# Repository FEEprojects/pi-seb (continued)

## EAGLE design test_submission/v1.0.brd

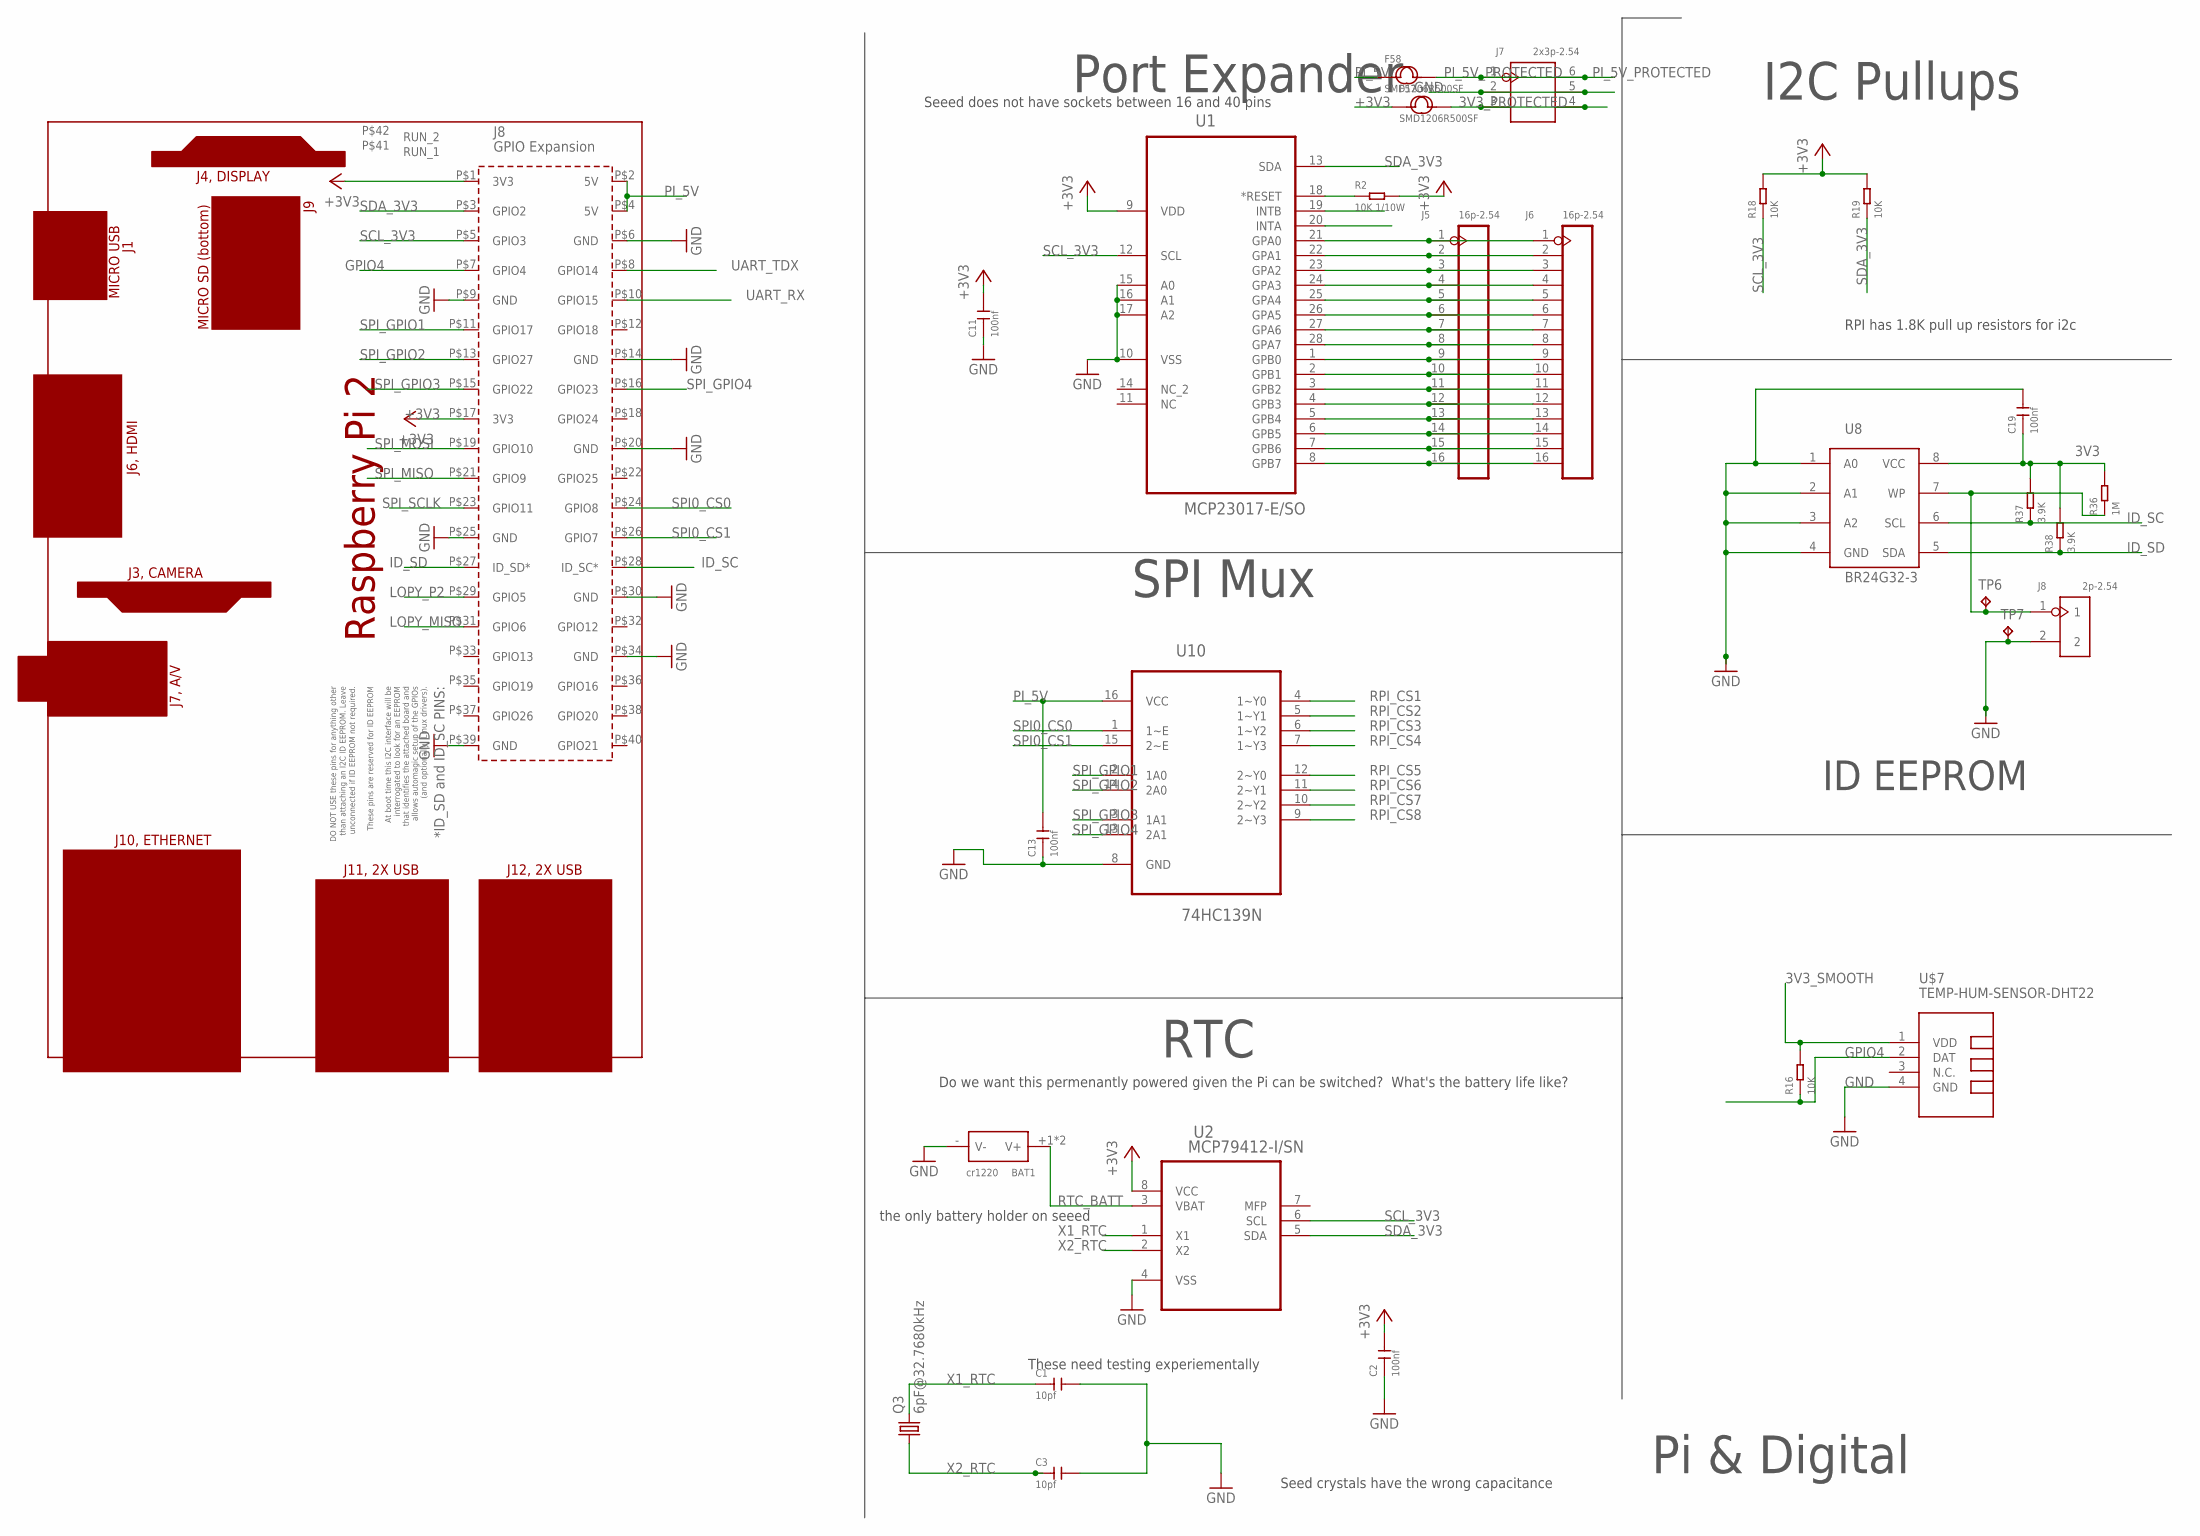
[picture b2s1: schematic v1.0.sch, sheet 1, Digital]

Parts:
BAT1: cr1220; BAT2P-13.5-CR1220
C1, C3: 10pf; C0603
C2, C11, C13, C19: 100nf; C0603
F57, F58: SMD1206R500SF; F1206
J5, J6: 16p-2.54; H16-2.54
J7: 2x3p-2.54; H2X3-2.54
J8: 2p-2.54; H2-2.54
PCB1: RPI2
Q3: 6pF@32.7680kHz; 86SMX
R2: 10K 1/10W; R0603
R16, R18, R19: 10K; R0603
R36: 1M; R0603
R37, R38: 3.9K; R0603
TP6, TP7: TPB2,54; B2,54
U1: MCP23017-E/SO; SOIC127P1032X265-28N
U2: MCP79412-I/SN; SOIC127P600X175-8N
U8: BR24G32-3; SOP8
U10: 74HC139N; DIP254P762X420-16
U$7: TEMP-HUM-SENSOR-DHT22

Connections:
3V3: C19.1, R36.2, R37.2, R38.2, U8.8 (VCC)
3V3_PROTECTED: F57.2, J7.3, J7.4
3V3_SMOOTH: R16.2, U$7.1 (VDD); also elsewhere on the board
+3V3: C2.2, C11.2, F57.1, PCB1.P$1 (3V3), PCB1.P$17 (3V3), R2.2, R18.2, R19.2, U1.9 (VDD), U2.8 (VCC); also elsewhere on the board
GND: BAT1.- (V-), C1.2, C2.1, C3.2, C11.1, C13.1, C19.2, J7.2, J7.5, J8.2, PCB1.P$6 (GND), PCB1.P$9 (GND), PCB1.P$14 (GND), PCB1.P$20 (GND), PCB1.P$25 (GND), PCB1.P$30 (GND), PCB1.P$34 (GND), PCB1.P$39 (GND), TP7.TP, U1.10 (VSS), U1.15 (A0), U1.16 (A1), U1.17 (A2), U2.4 (VSS), U8.1 (A0), U8.2 (A1), U8.3 (A2), U8.4 (GND), U10.8 (GND), U$7.4 (GND); also elsewhere on the board
GPIO4: PCB1.P$7 (GPIO4), R16.1, U$7.2 (DAT)
ID_SC: PCB1.P$28 (ID_SC*), R37.1, U8.6 (SCL)
ID_SD: PCB1.P$27 (ID_SD*), R38.1, U8.5 (SDA)
LOPY_MISO: PCB1.P$31 (GPIO6); also elsewhere on the board
LOPY_P2: PCB1.P$29 (GPIO5); also elsewhere on the board
unnamed: R2.1, U1.18 (*RESET)
unnamed: J5.1, J6.1, U1.21 (GPA0)
unnamed: J5.2, J6.2, U1.22 (GPA1)
unnamed: J5.3, J6.3, U1.23 (GPA2)
unnamed: J5.4, J6.4, U1.24 (GPA3)
unnamed: J5.5, J6.5, U1.25 (GPA4)
unnamed: J5.6, J6.6, U1.26 (GPA5)
unnamed: J5.7, J6.7, U1.27 (GPA6)
unnamed: J5.8, J6.8, U1.28 (GPA7)
unnamed: J5.9, J6.9, U1.1 (GPB0)
unnamed: J5.10, J6.10, U1.2 (GPB1)
unnamed: J5.11, J6.11, U1.3 (GPB2)
unnamed: J5.12, J6.12, U1.4 (GPB3)
unnamed: J5.13, J6.13, U1.5 (GPB4)
unnamed: J5.14, J6.14, U1.6 (GPB5)
unnamed: J5.15, J6.15, U1.7 (GPB6)
unnamed: J5.16, J6.16, U1.8 (GPB7)
unnamed: J8.1, R36.1, TP6.TP, U8.7 (WP)
PI_5V: C13.2, F58.1, PCB1.P$2 (5V), PCB1.P$4 (5V), U10.16 (VCC); also elsewhere on the board
PI_5V_PROTECTED: F58.2, J7.1, J7.6
RPI_CS1: U10.4 (1~Y0); also elsewhere on the board
RPI_CS2: U10.5 (1~Y1); also elsewhere on the board
RPI_CS3: U10.6 (1~Y2); also elsewhere on the board
RPI_CS4: U10.7 (1~Y3); also elsewhere on the board
RPI_CS5: U10.12 (2~Y0); also elsewhere on the board
RPI_CS6: U10.11 (2~Y1); also elsewhere on the board
RPI_CS7: U10.10 (2~Y2); also elsewhere on the board
RPI_CS8: U10.9 (2~Y3); also elsewhere on the board
RTC_BATT: BAT1.+1 (V+), BAT1.+2 (V+), U2.3 (VBAT)
SCL_3V3: PCB1.P$5 (GPIO3), R18.1, U1.12 (SCL), U2.6 (SCL); also elsewhere on the board
SDA_3V3: PCB1.P$3 (GPIO2), R19.1, U1.13 (SDA), U2.5 (SDA); also elsewhere on the board
SPI0_CS0: PCB1.P$24 (GPIO8), U10.1 (1~E)
SPI0_CS1: PCB1.P$26 (GPIO7), U10.15 (2~E)
SPI_GPIO1: PCB1.P$11 (GPIO17), U10.2 (1A0)
SPI_GPIO2: PCB1.P$13 (GPIO27), U10.14 (2A0)
SPI_GPIO3: PCB1.P$15 (GPIO22), U10.3 (1A1)
SPI_GPIO4: PCB1.P$16 (GPIO23), U10.13 (2A1)
SPI_MISO: PCB1.P$21 (GPIO9); also elsewhere on the board
SPI_MOSI: PCB1.P$19 (GPIO10); also elsewhere on the board
SPI_SCLK: PCB1.P$23 (GPIO11); also elsewhere on the board
UART_RX: PCB1.P$10 (GPIO15); also elsewhere on the board
UART_TDX: PCB1.P$8 (GPIO14); also elsewhere on the board
X1_RTC: C1.1, Q3.4 (2), U2.1 (X1)
X2_RTC: C3.1, Q3.1, U2.2 (X2)

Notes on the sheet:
Pi & Digital
Port Expander
SPI Mux
RTC
I2C Pullups
Do we want this permenantly powered given the Pi can be switched? What's the battery life like?
Seed crystals have the wrong capacitance
These need testing experiementally
Seeed does not have sockets between 16 and 40 pins
RPI has 1.8K pull up resistors for i2c
the only battery holder on seeed
ID EEPROM

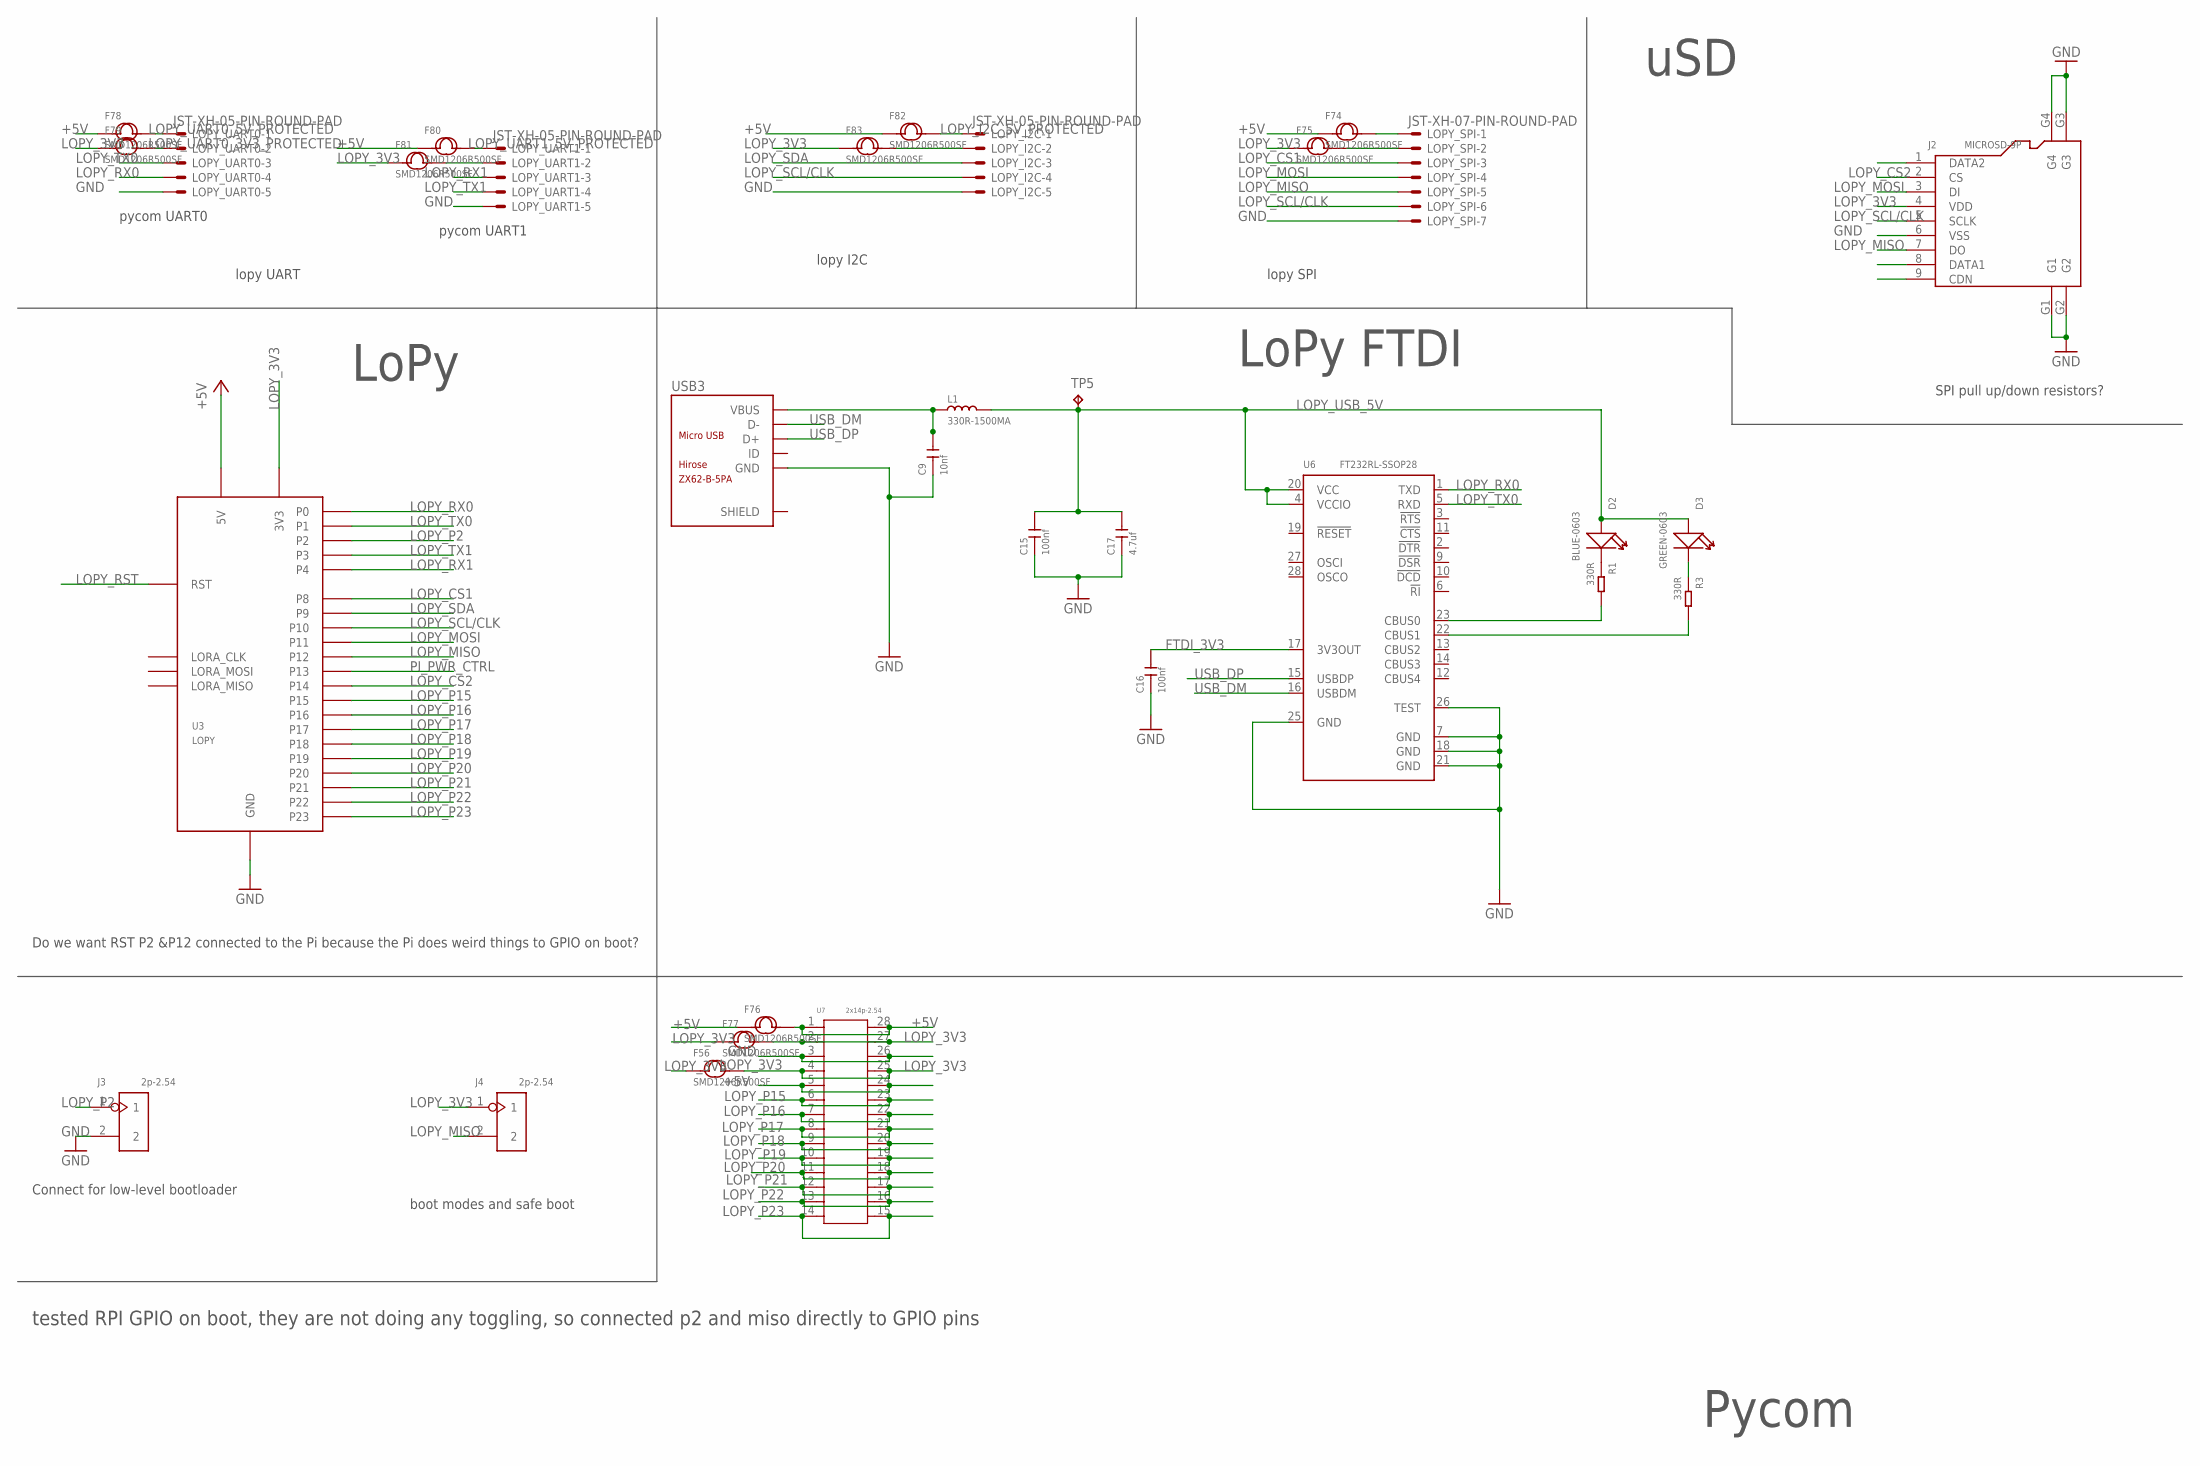
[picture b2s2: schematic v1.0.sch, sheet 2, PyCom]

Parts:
C9: 10nf; C0805
C15, C16: 100nf; C0603
C17: 4.7uf; C0603
D2: BLUE-0603; LED-0603
D3: GREEN-0603; LED-0603
F56, F74, F75, F76, F77, F78, F79, F80, F81, F82, F83: SMD1206R500SF; F1206
J2: MICROSD-9P; MICRO-SD9+4P-SMD-16.1X14.5X1.85MM
J3, J4: 2p-2.54; H2-2.54
L1: 330R-1500MA; L0805
LOPY_I2C: JST-XH-05-PIN-ROUND-PAD; JST-XH-05-PACKAGE-ROUND-PAD
LOPY_SPI: JST-XH-07-PIN-ROUND-PAD; JST-XH-07-PACKAGE-ROUND-PAD
LOPY_UART0, LOPY_UART1: JST-XH-05-PIN-ROUND-PAD; JST-XH-05-PACKAGE-ROUND-PAD
R1, R3: 330R; R0603
TP5: TPB2,54; B2,54
U3: LOPY
U6: FT232RL-SSOP28; SSOP28-0.65-10.2X5.2MM
U7: 2x14p-2.54; SCK28-2.54-35.6X10MM
USB3: ZX62-B-5PA; MICRO-USB5+6P-SMD-0.65-AB

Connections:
+5V: F74.1, F76.1, F76.2, F78.1, F80.1, F82.1, U3.P$28 (5V), U7.1, U7.5, U7.24, U7.28; also elsewhere on the board
FTDI_3V3: C16.2, U6.17 (3V3OUT); also elsewhere on the board
GND: C9.1, C15.1, C16.1, C17.1, J2.6 (VSS), J2.G1, J2.G2, J2.G3, J2.G4, J3.2, LOPY_I2C.5, LOPY_SPI.7, LOPY_UART0.5, LOPY_UART1.5, U3.P$27 (GND), U6.7 (GND), U6.18 (GND), U6.21 (GND), U6.25 (GND), U6.26 (TEST), U7.3, U7.26, USB3.5 (GND); also elsewhere on the board
LOPY_3V3: F56.1, F56.2, F75.1, F77.1, F77.2, F79.1, F81.1, F83.1, J2.4 (VDD), J4.1, U3.P$26 (3V3), U7.2, U7.4, U7.25, U7.27; also elsewhere on the board
LOPY_CS1: LOPY_SPI.3, U3.P$10 (P8)
LOPY_CS2: J2.2 (CS), U3.P$16 (P14)
LOPY_I2C_3V3_PROTECTED: F83.2, LOPY_I2C.2
LOPY_I2C_5V_PROTECTED: F82.2, LOPY_I2C.1
LOPY_MISO: J2.7 (DO), J4.2, LOPY_SPI.5, U3.P$14 (P12); also elsewhere on the board
LOPY_MOSI: J2.3 (DI), LOPY_SPI.4, U3.P$13 (P11)
LOPY_P2: J3.1, U3.P$4 (P2); also elsewhere on the board
LOPY_P15: U3.P$17 (P15), U7.6, U7.23
LOPY_P16: U3.P$18 (P16), U7.7, U7.22
LOPY_P17: U3.P$19 (P17), U7.8, U7.21
LOPY_P18: U3.P$20 (P18), U7.9, U7.20
LOPY_P19: U3.P$21 (P19), U7.10, U7.19
LOPY_P20: U3.P$22 (P20), U7.11, U7.18
LOPY_P21: U3.P$23 (P21), U7.12, U7.17
LOPY_P22: U3.P$24 (P22), U7.13, U7.16
LOPY_P23: U3.P$25 (P23), U7.14, U7.15
LOPY_RST: U3.P$1 (RST)
LOPY_RX0: LOPY_UART0.4, U3.P$2 (P0), U6.1 (TXD)
LOPY_RX1: LOPY_UART1.3, U3.P$6 (P4)
LOPY_SCL/CLK: J2.5 (SCLK), LOPY_I2C.4, LOPY_SPI.6, U3.P$12 (P10)
LOPY_SDA: LOPY_I2C.3, U3.P$11 (P9)
LOPY_SPI_3V3_PROTECTED: F75.2, LOPY_SPI.2
LOPY_SPI_5V_PROTECTED: F74.2, LOPY_SPI.1
LOPY_TX0: LOPY_UART0.3, U3.P$3 (P1), U6.5 (RXD)
LOPY_TX1: LOPY_UART1.4, U3.P$5 (P3)
LOPY_UART0_3V3_PROTECTED: F79.2, LOPY_UART0.2
LOPY_UART0_5V_PROTECTED: F78.2, LOPY_UART0.1
LOPY_UART1_3V3_PROTECTED: F81.2, LOPY_UART1.2
LOPY_UART1_5V_PROTECTED: F80.2, LOPY_UART1.1
LOPY_USB_5V: C15.2, C17.2, D2.+, D3.+, L1.2, TP5.TP, U6.4 (VCCIO), U6.20 (VCC); also elsewhere on the board
unnamed: D2.-, R1.1
unnamed: D3.-, R3.1
unnamed: R1.2, U6.23 (CBUS0)
unnamed: R3.2, U6.22 (CBUS1)
PI_PWR_CTRL: U3.P$15 (P13); also elsewhere on the board
USB_DM: U6.16 (USBDM), USB3.2 (D-)
USB_DP: U6.15 (USBDP), USB3.3 (D+)
VBUS: C9.2, L1.1, USB3.1 (VBUS)

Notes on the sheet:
Pycom
pycom UART1
pycom UART0
lopy I2C
lopy SPI
lopy UART
Do we want RST P2 &P12 connected to the Pi because the Pi does weird things to GPIO on boot?
SPI pull up/down resistors?
LoPy
uSD
LoPy FTDI
Connect for low-level bootloader
boot modes and safe boot
tested RPI GPIO on boot, they are not doing any toggling, so connected p2 and miso directly to GPIO pins

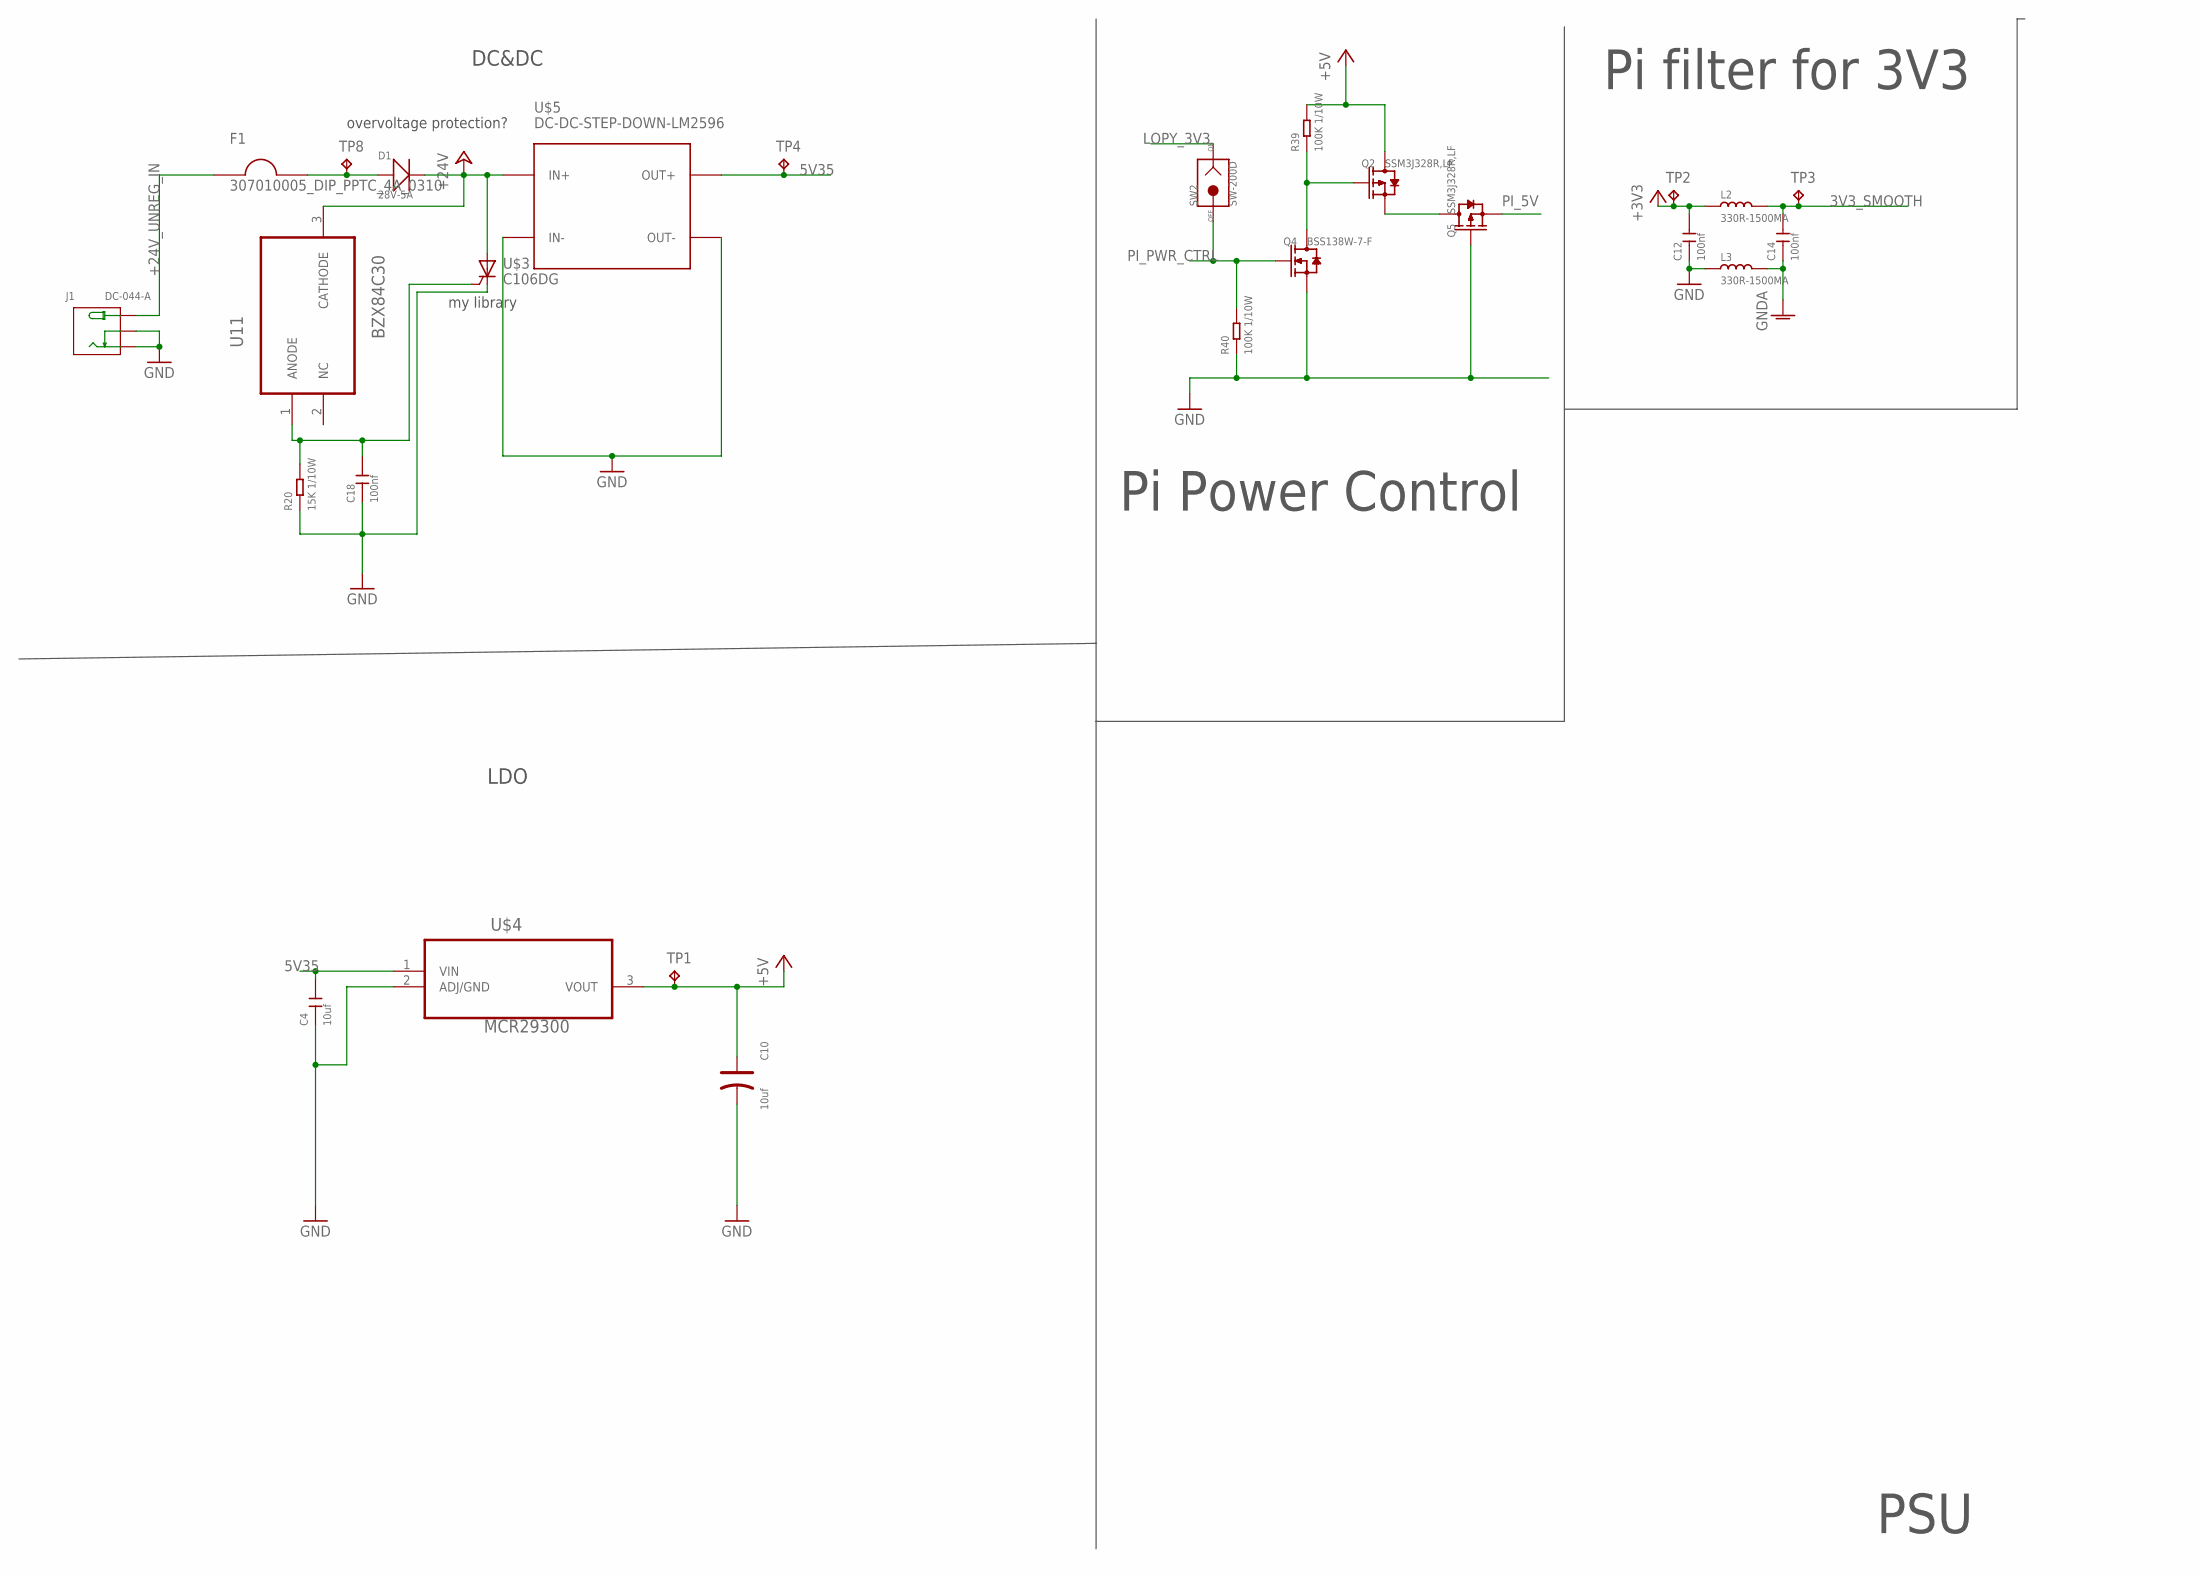
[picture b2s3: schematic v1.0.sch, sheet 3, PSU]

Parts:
C4: 10uf; C0603
C10: 10uf; AVX-A
C12, C14, C18: 100nf; C0603
D1: 28V-5A; DO-214AA
F1: 307010005_DIP_PPTC_4A_0310; TH_5MM_14MM
J1: DC-044-A; DCJ3P-11.6X9.6X7.0MM
L2, L3: 330R-1500MA; L0805
Q2, Q5: SSM3J328R,LF; SOT-23
Q4: BSS138W-7-F; SOT-23
R20: 15K 1/10W; R0603
R39, R40: 100K 1/10W; R0603
SW2: SW-200D; SW2-12.7-12.0X3.6X3.6MM
TP1, TP2, TP3, TP4, TP8: TPB2,54; B2,54
U11: BZX84C30; SOT91P240X110-3N
U$3: C106DG; TO-225AA
U$4: MCR29300; TO-263
U$5: DC-DC-STEP-DOWN-LM2596

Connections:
3V3_SMOOTH: C14.2, L2.2, TP3.TP; also elsewhere on the board
5V35: C4.2, TP4.TP, U$4.1 (VIN), U$5.OUT+; also elsewhere on the board
+3V3: C12.2, L2.1, TP2.TP; also elsewhere on the board
+5V: C10.+, Q2.3 (D), R39.2, TP1.TP, U$4.3 (VOUT); also elsewhere on the board
+24V: D1.-, U11.3 (CATHODE), U$3.1 (A), U$5.IN+; also elsewhere on the board
+24V_UNREG_IN: F1.P$1, J1.+
GND: C4.1, C10.-, C12.1, C18.1, J1.-, J1.CDN, L3.1, Q4.2 (S), Q5.1 (G), R20.1, R40.1, U$3.2 (C), U$4.2 (ADJ/GND), U$5.IN-, U$5.OUT-; also elsewhere on the board
GNDA: C14.1, L3.2; also elsewhere on the board
LOPY_3V3: SW2.1; also elsewhere on the board
unnamed: D1.+, F1.P$2, TP8.TP
unnamed: C18.2, R20.2, U11.1 (ANODE), U$3.3 (G1)
unnamed: Q2.2 (S), Q5.3 (D)
unnamed: Q2.1 (G), Q4.3 (D), R39.1
PI_5V: Q5.2 (S); also elsewhere on the board
PI_PWR_CTRL: Q4.1 (G), R40.2, SW2.2; also elsewhere on the board

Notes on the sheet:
PSU
LDO
DC&DC
Pi filter for 3V3
overvoltage protection?
Pi Power Control
my library

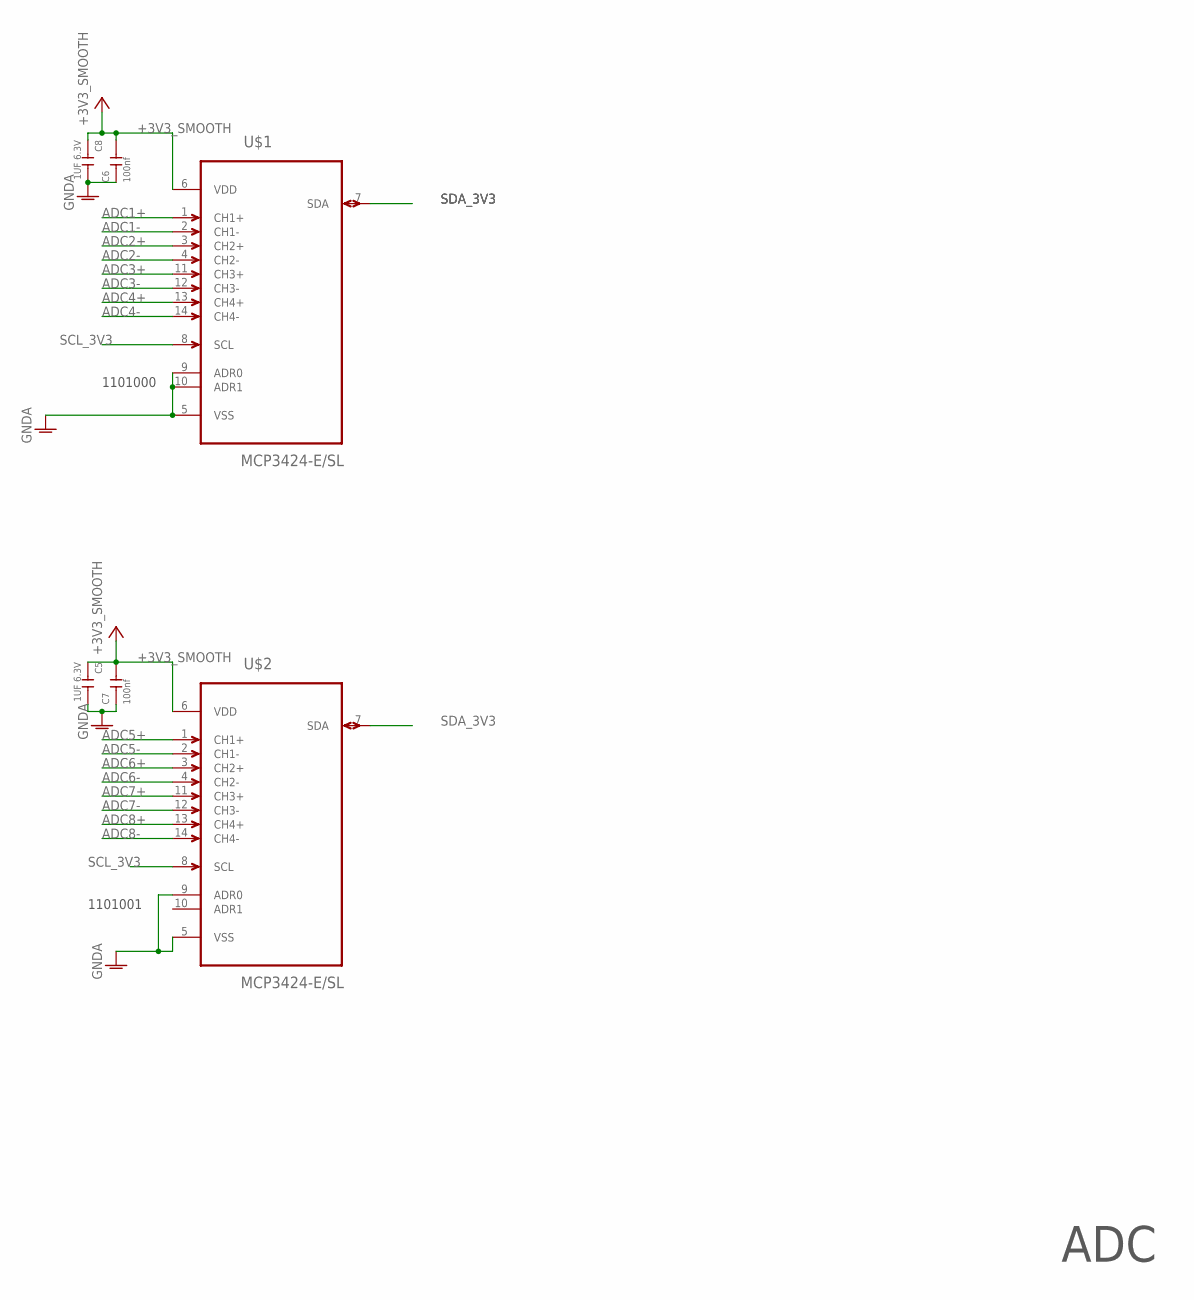
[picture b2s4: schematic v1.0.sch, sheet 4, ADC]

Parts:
C5, C8: 1UF 6.3V; C0402
C6, C7: 100nf; C0603
U$1, U$2: MCP3424-E/SL; SOIC127P600X175-14N

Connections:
+3V3_SMOOTH: C5.1, C6.2, C7.2, C8.1, U$1.6 (VDD), U$2.6 (VDD)
ADC1+: U$1.1 (CH1+); also elsewhere on the board
ADC1-: U$1.2 (CH1-); also elsewhere on the board
ADC2+: U$1.3 (CH2+); also elsewhere on the board
ADC2-: U$1.4 (CH2-); also elsewhere on the board
ADC3+: U$1.11 (CH3+); also elsewhere on the board
ADC3-: U$1.12 (CH3-); also elsewhere on the board
ADC4+: U$1.13 (CH4+); also elsewhere on the board
ADC4-: U$1.14 (CH4-); also elsewhere on the board
ADC5+: U$2.1 (CH1+); also elsewhere on the board
ADC5-: U$2.2 (CH1-); also elsewhere on the board
ADC6+: U$2.3 (CH2+); also elsewhere on the board
ADC6-: U$2.4 (CH2-); also elsewhere on the board
ADC7+: U$2.11 (CH3+); also elsewhere on the board
ADC7-: U$2.12 (CH3-); also elsewhere on the board
ADC8+: U$2.13 (CH4+); also elsewhere on the board
ADC8-: U$2.14 (CH4-); also elsewhere on the board
GNDA: C5.2, C6.1, C7.1, C8.2, U$1.5 (VSS), U$1.9 (ADR0), U$1.10 (ADR1), U$2.5 (VSS), U$2.9 (ADR0); also elsewhere on the board
SCL_3V3: U$1.8 (SCL), U$2.8 (SCL); also elsewhere on the board
SDA_3V3: U$1.7 (SDA), U$2.7 (SDA); also elsewhere on the board

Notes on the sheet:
ADC
1101000
1101001

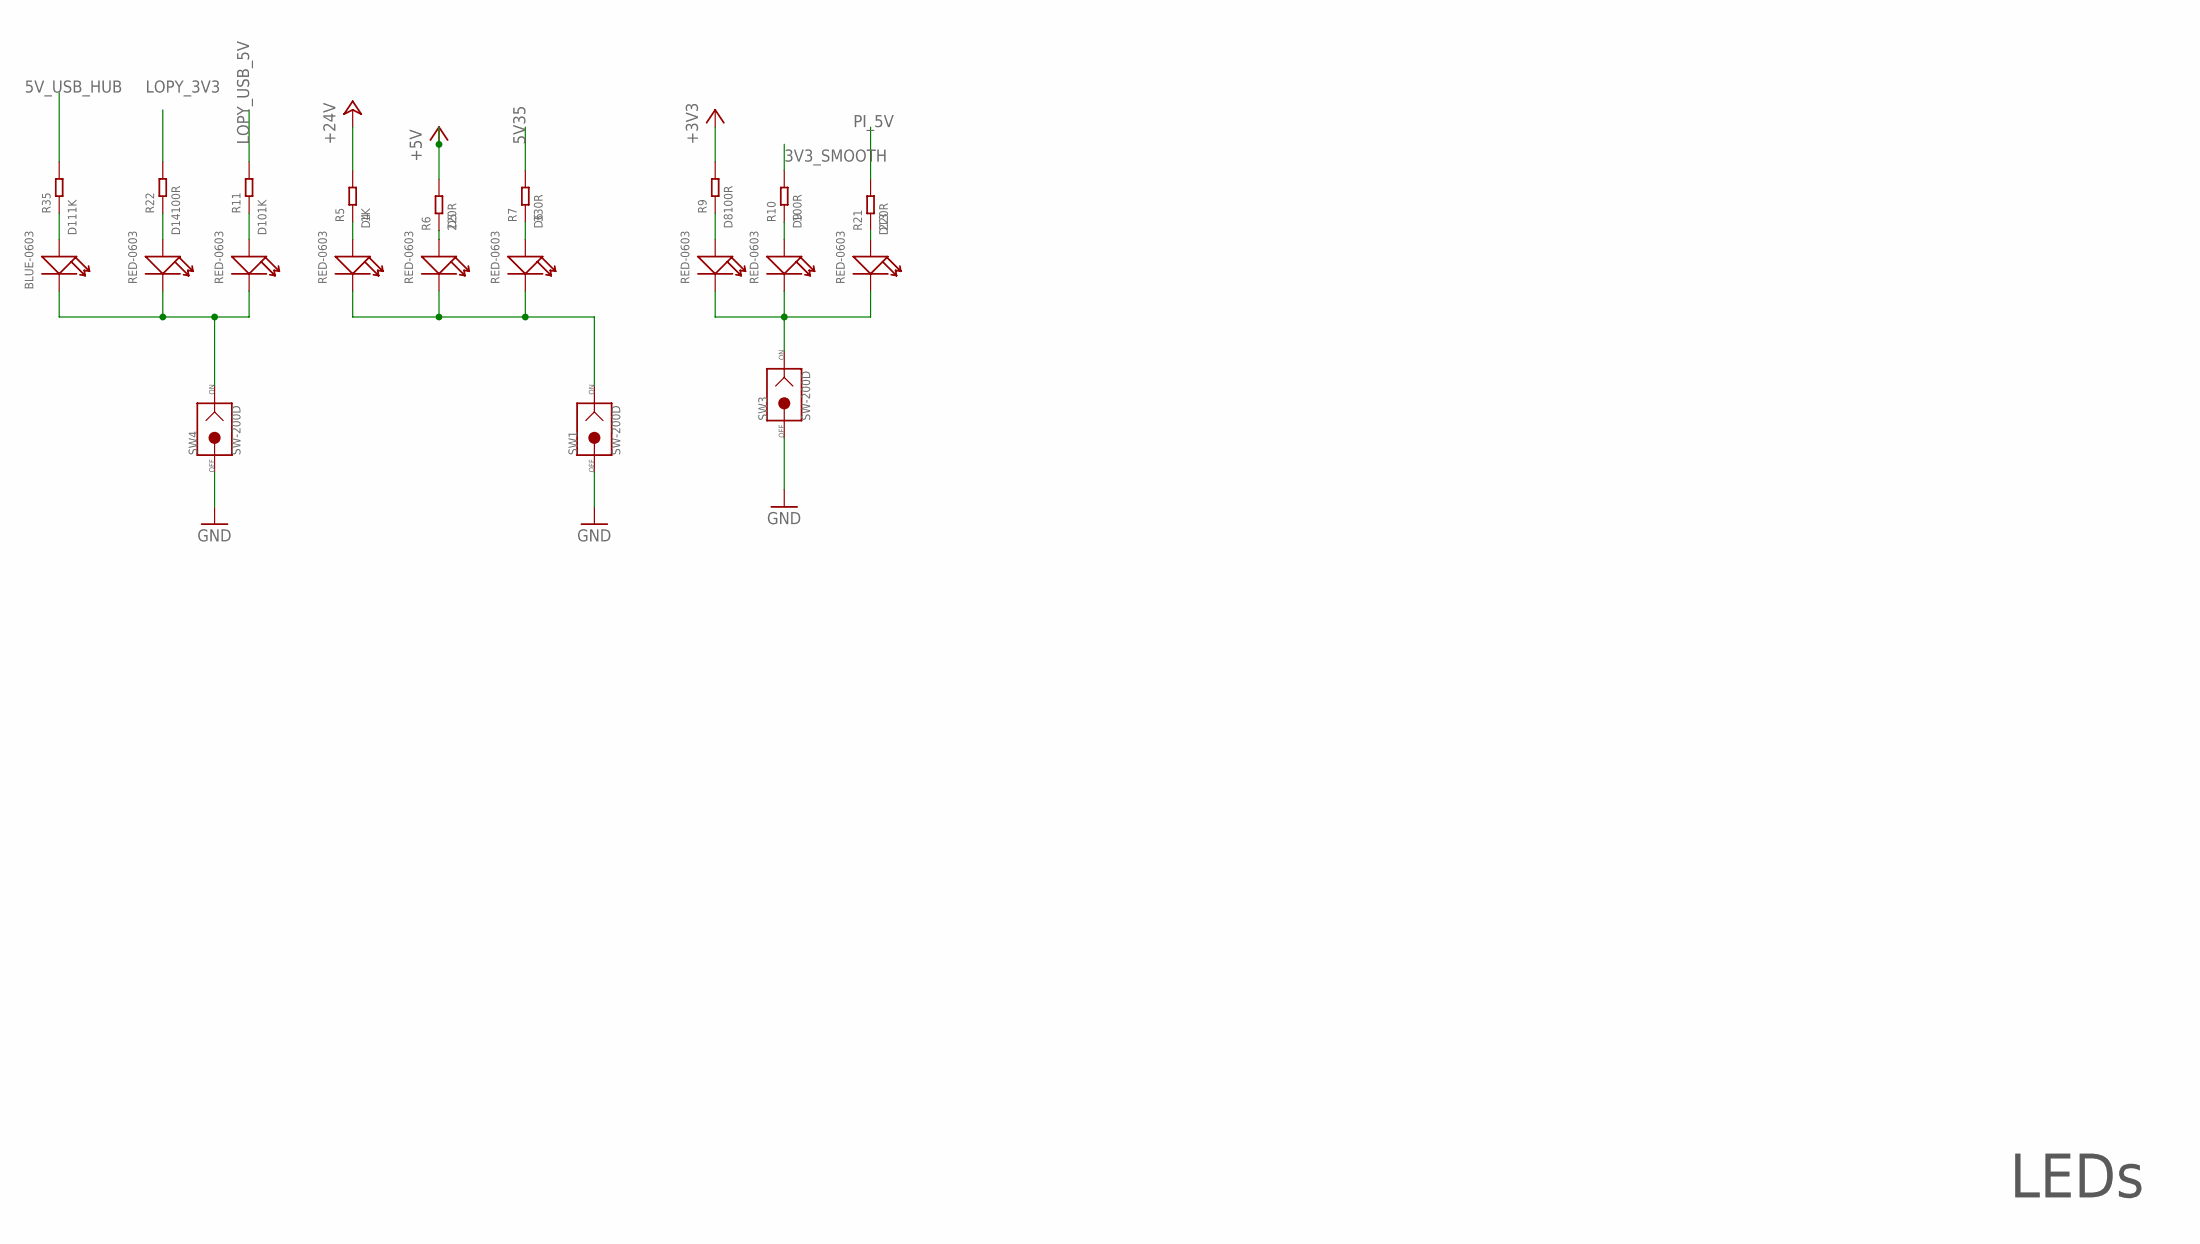
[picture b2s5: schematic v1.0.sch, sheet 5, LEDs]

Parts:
D4, D5, D6, D8, D9, D10, D13, D14: RED-0603; LED-0603
D11: BLUE-0603; LED-0603
R5, R11, R35: 1K; R0603
R6, R21: 220R; R0603
R7: 330R; R0603
R9, R10, R22: 100R; R0603
SW1, SW3, SW4: SW-200D; SW2-12.7-12.0X3.6X3.6MM

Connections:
3V3_SMOOTH: R10.2; also elsewhere on the board
5V35: R7.2; also elsewhere on the board
5V_USB_HUB: R35.2; also elsewhere on the board
+3V3: R9.2; also elsewhere on the board
+5V: R6.2; also elsewhere on the board
+24V: R5.2; also elsewhere on the board
GND: SW1.2, SW3.2, SW4.2; also elsewhere on the board
LOPY_3V3: R22.2; also elsewhere on the board
LOPY_USB_5V: R11.2; also elsewhere on the board
unnamed: D9.+, R10.1
unnamed: D8.+, R9.1
unnamed: D6.+, R7.1
unnamed: D5.+, R6.1
unnamed: D4.+, R5.1
unnamed: D11.+, R35.1
unnamed: D10.+, R11.1
unnamed: D4.-, D5.-, D6.-, SW1.1
unnamed: D14.+, R22.1
unnamed: D10.-, D11.-, D14.-, SW4.1
unnamed: D8.-, D9.-, D13.-, SW3.1
unnamed: D13.+, R21.1
PI_5V: R21.2; also elsewhere on the board

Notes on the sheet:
LEDs
